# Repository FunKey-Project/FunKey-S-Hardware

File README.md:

## FunKey S Hardware
This repository contains all the hardware design and production files required to build the [FunKey-S retro-gaming console](https://www.funkey-project.com/) electronic PCBA using the [KiCAD ECAD tools](https://kicad.org/).

If you don't want to install these tools but still want to get an idea of what it looks like, you can check the [schematics](https://github.com/FunKey-Project/FunKey-S-Hardware/blob/master/PDF/FunKey%20Schematics.pdf) and the [layout](https://github.com/FunKey-Project/FunKey-S-Hardware/blob/master/PDF/FunKey%20PCB.pdf) in PDF format, the interactive [BOM](https://github.com/FunKey-Project/FunKey-S-Hardware/tree/master/BOM) is directly in HTML format, you can download it and display it in a browser.

The FunKey S is a small foldable retro-gaming console.

Its electronic parts consist in:
 - 1x main PCB (0.8 mm thickness) with components on both sides, the maximum component height above PCB on both sides is 1.5 mm. Current revision for this board is Revision E
 - 1x 1.54” IPS LCD TFT screen with SPI interface and using a custom flex cable
 - 1x 420 mAh 402540 LiPo battery

The FunKey S PCBA Rev. E contains the following main components:
 - 1x Allwinner V3s SoC with integrated 64MB DDR2 DRAM (LQFP128 package)
 - 1x X-Powers AXP209 companion PMIC chip to provide almost all required power supply rails (QFN48 package)
 - 1x Sylergy SY8088 Buck DC/DC SMPS chip to provide the DRAM power supply rail (SOT23-5 package)
 - 1x NXP PCAL6416 I2C GPIO expander to control all buttons and keypads (except Power Key) (QFN24 package)
 - 1x Diodes Inc. PAM8301 mono audio amplifier (TSOT26 package)
 - 1x 24 MHz main crystal
 - 1x 32.768 kHz RTC crystal
 - 1x Standex-Meder MK24 Reed switch for magnet proximity detection
 - 1x LED for charge indication
 - 1x 8 Ω 0.3 W built-in speaker
 - 1x Micro USB edge-mounted connector
 - 1x Micro SD (TF Card) Push/Push low-profile connector
 - 1x Hirose DF37 0.4 mm pitch miniature LCD connector
 - 1x JST 1 mm pitch battery connector
 - 1x 1.27 mm pitch debug UART header (not mounted)

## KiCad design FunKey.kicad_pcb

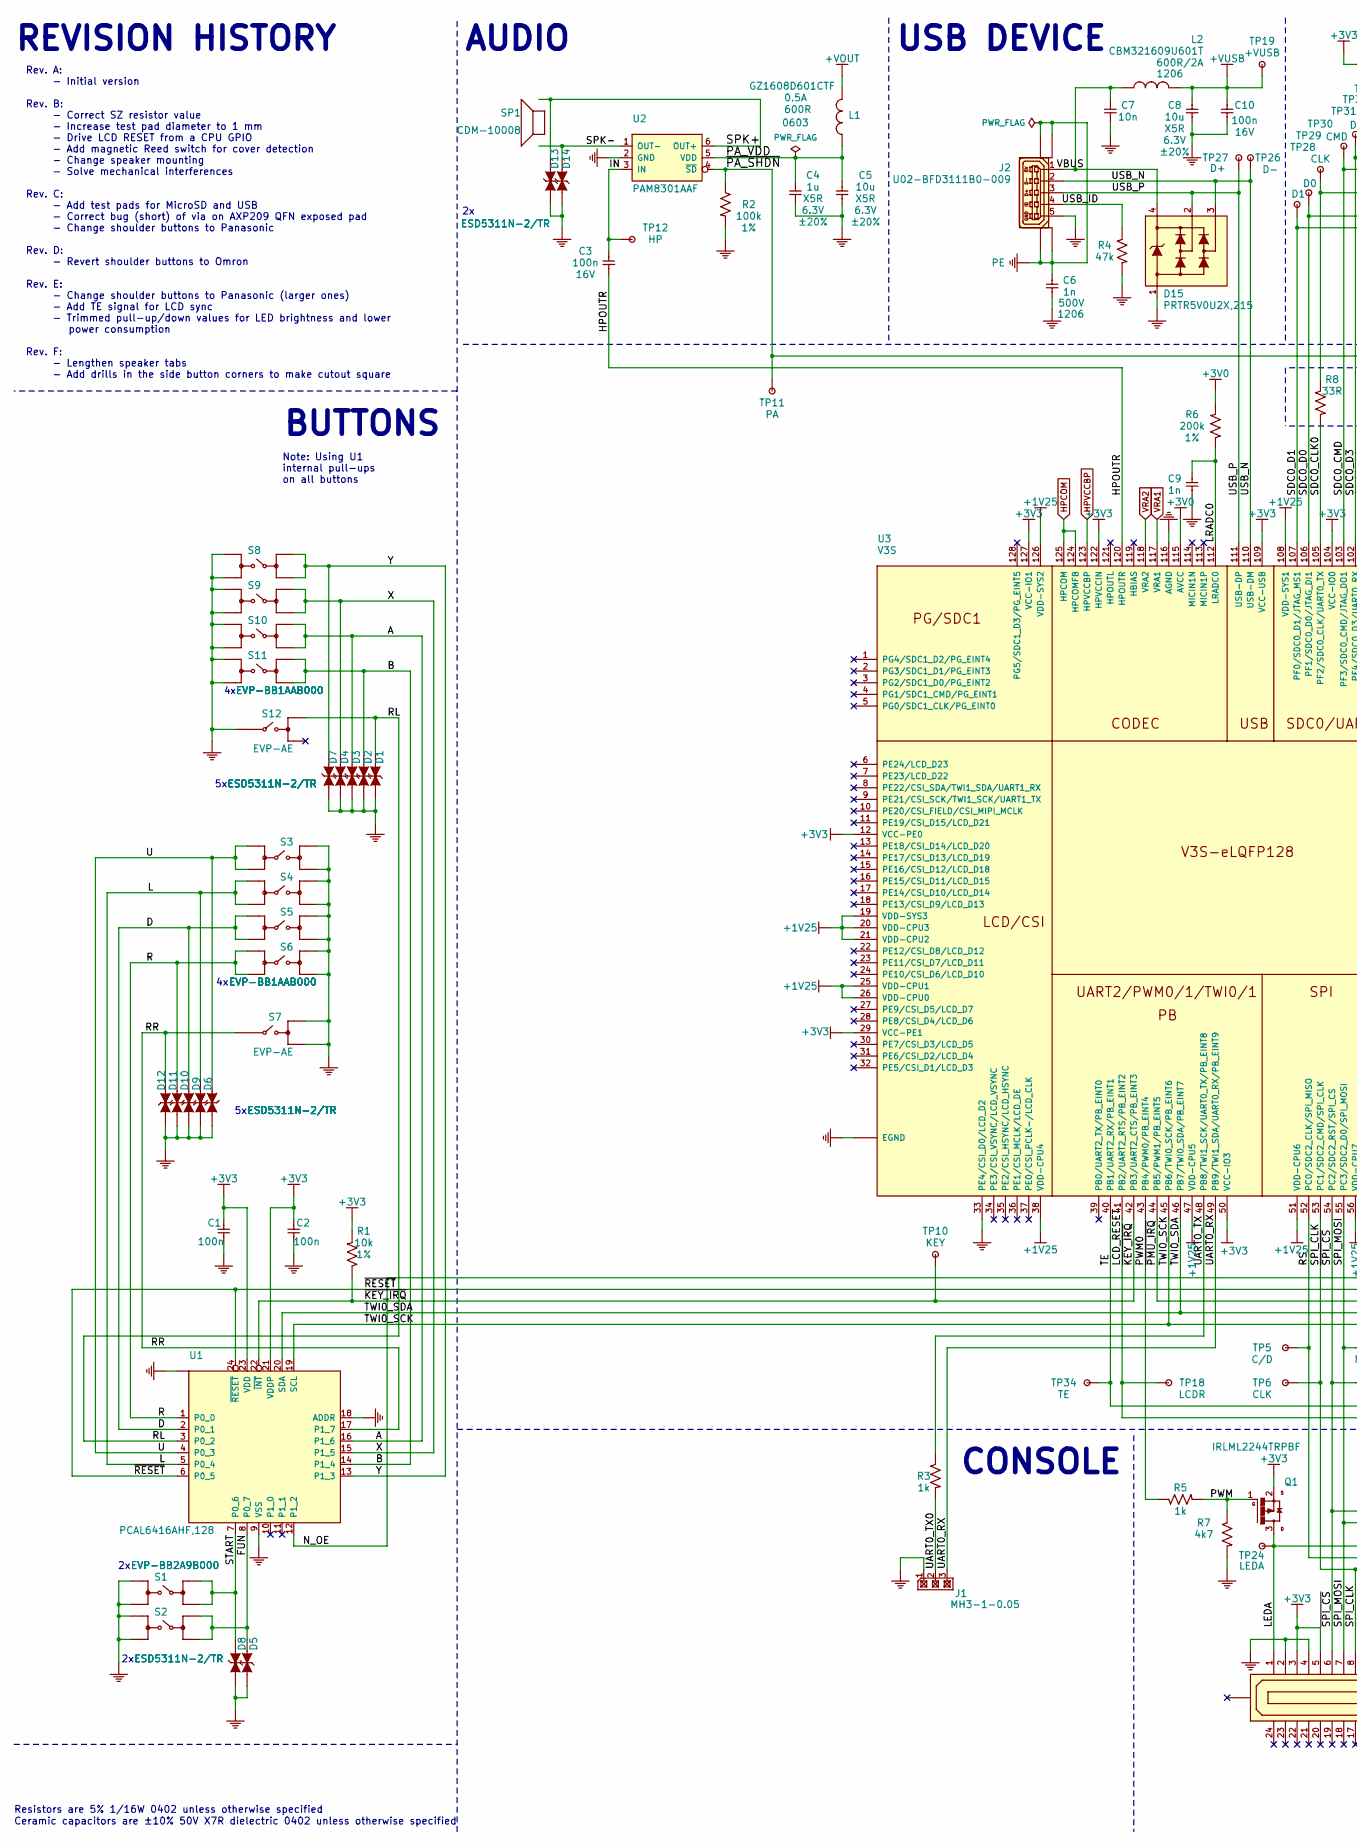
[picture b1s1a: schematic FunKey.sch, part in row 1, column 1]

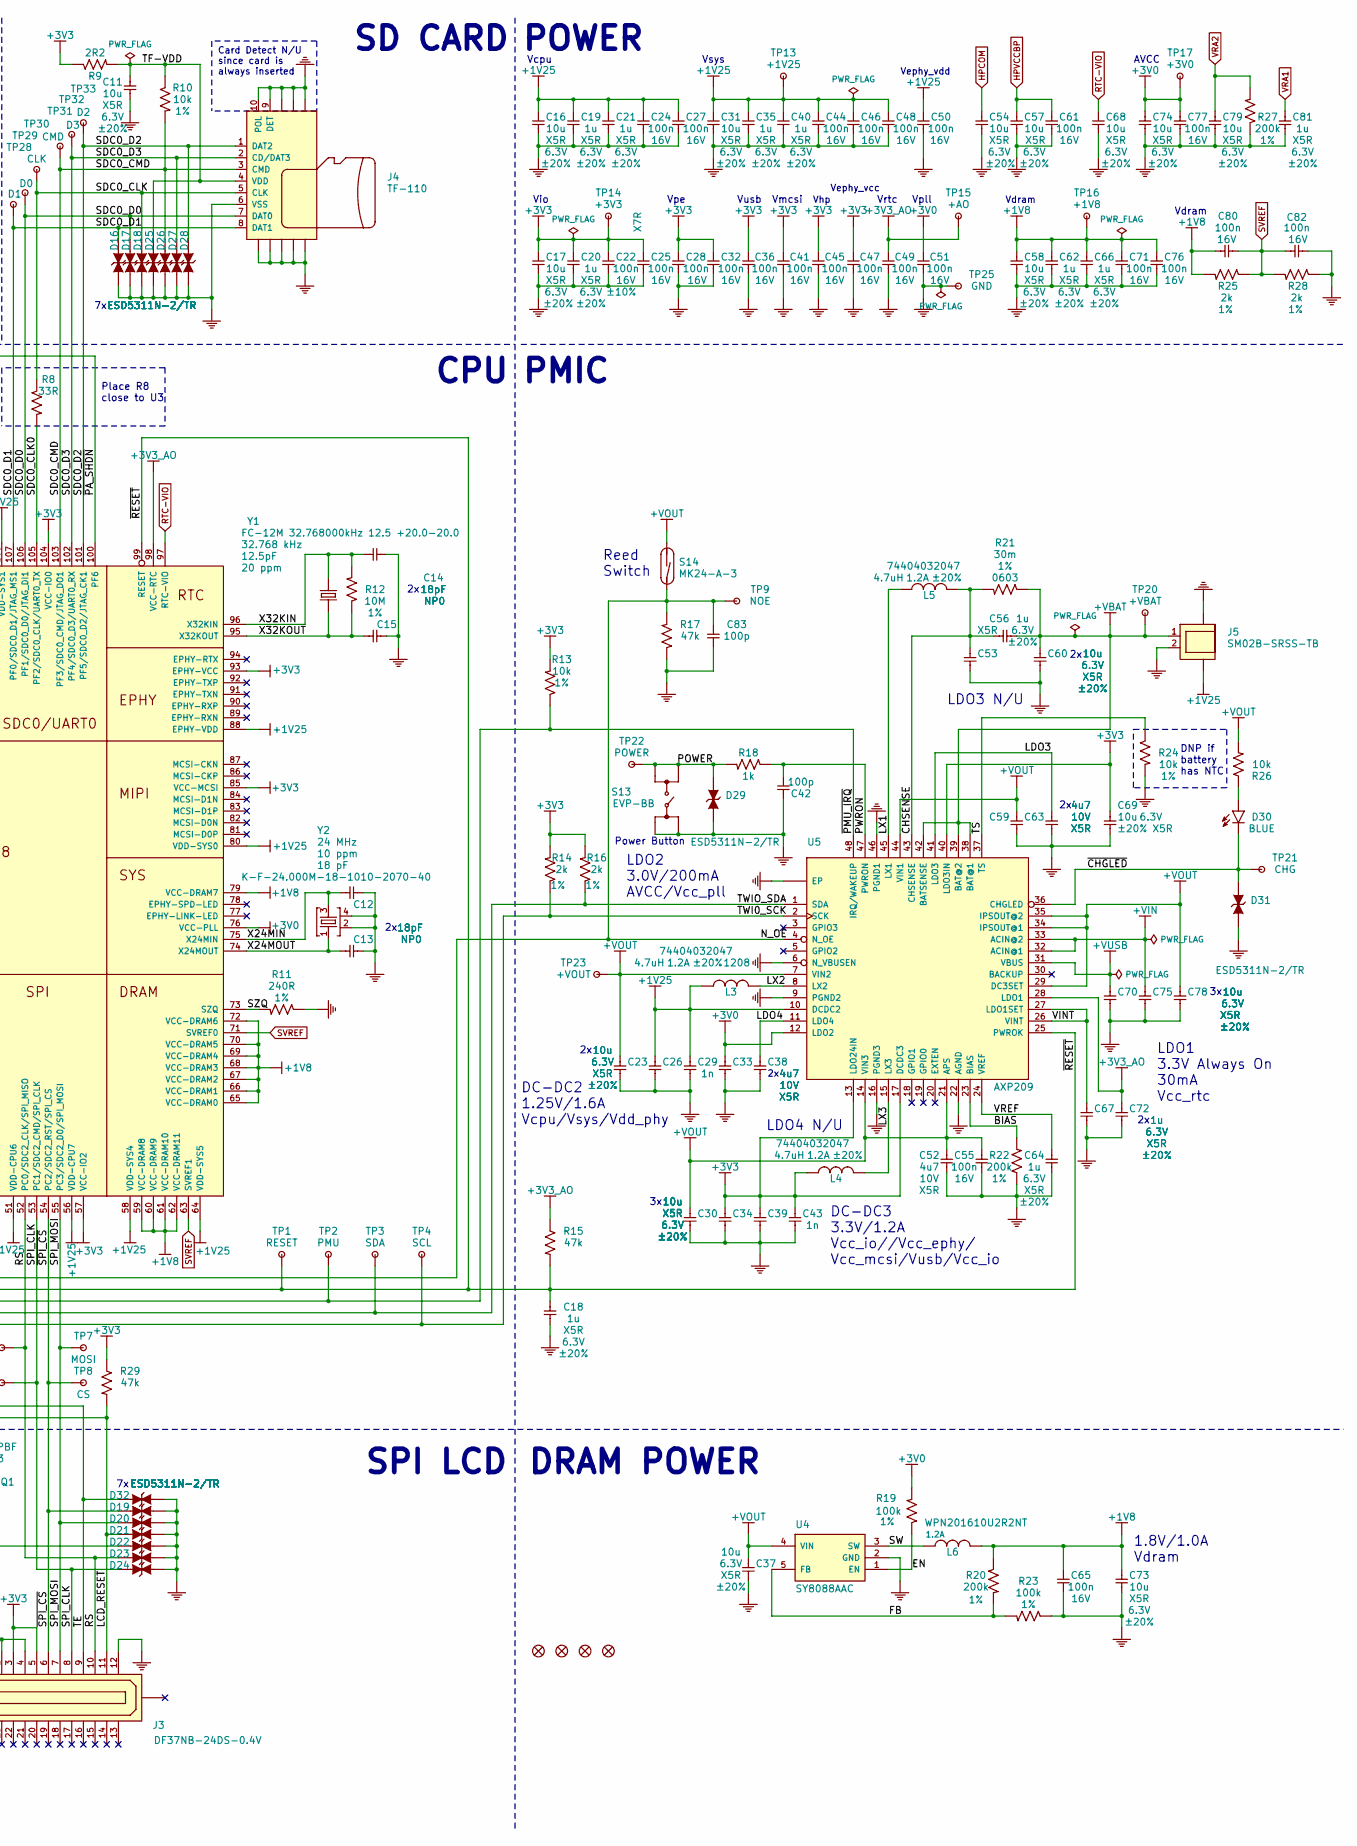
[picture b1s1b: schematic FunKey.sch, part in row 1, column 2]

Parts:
C1, C2, C3, C10, C22, C24, C25, C27, C28, C32, C36, C41, C44, C45, C46, C47, C48, C49, C50, C51, C55, C61, C65, C71, C76, C77, C80, C82: 100n; C0402; PARTNO C0402_100n_X7R_10%_CER_16V
C4, C18, C19, C20, C21, C35, C40, C56, C62, C64, C66, C67, C72, C81: 1u; C0402; PARTNO C0402_1u_X5R_20%_CER_6V3
C5, C8, C11, C16, C17, C23, C26, C30, C31, C34, C37, C39, C53, C54, C57, C58, C60, C68, C69, C70, C73, C74, C75, C78, C79: 10u; C0402; PARTNO C0402_10u_X5R_20%_CER_6V3
C6: 1n; C1206; PARTNO C1206_1n_X7R_10%_CER_500V
C7: 10n; C0402; PARTNO C0402_10n_X7R_10%_CER_50V
C9, C29, C43: 1n; C0402; PARTNO C0402_1n_X7R_10%_CER_50V
C12, C13, C14, C15: 18pF; C0402; PARTNO C0402_18p_NP0_5%_CER_50V
C33, C38, C52, C59, C63: 4u7; C0402; PARTNO C0402_4u7_X5R_10%_CER_10V
C42, C83: 100p; C0402; PARTNO C0402_100p_X7R_10%_CER_50V
D1, D2, D3, D4, D5, D6, D7, D8, D9, D10, D11, D13, D14, D16, D17, D18, D19, D20, D21, D22, D23, D24, D25, D26, D27, D28, D29, D31, D32: ESD5311N-2/TR; ESD0402; PARTNO ESD0402_5V5_BIDIR
D12: ESD5311N-2/TR; ESD0402
D15: PRTR5V0U2X,215; SOT143B; PARTNO PRTR5V0U2X,215
D30: BLUE; LED0402; PARTNO LED0402-BLUE
F1, F2, F3, F4: FIDUCIAL
J1: MH3-1-0.05; PARTNO MH3-1-0.05
J2: U02-BFD3111B0-009; PARTNO U02-BFD3111B0-009
J3: DF37NB-24DS-0.4V; PARTNO DF37NB-24DS-0.4V
J4: TF-110; PARTNO TF-110
J5: SM02B-SRSS-TB; PARTNO SM02B-SRSS-TB
L1: GZ1608D601CTF; FB0603; PARTNO FB0603_600R_25%
L2: CBM321609U601T; FB1206; PARTNO FB1206_600R_25%
L3, L4, L5: 74404032047; WE-LQS; PARTNO 74404032047
L6: WPN201610U2R2NT; L1008; PARTNO L1008
Q1: IRLML2244TRPBF; SOT23-3; PARTNO IRLML2244TRPBF
R1, R10, R13, R24, R26: 10k; R0402; PARTNO R0402_10k_1%_62.5mW
R2, R19, R23: 100k; R0402; PARTNO R0402_100k_1%_62.5mW
R3, R5, R18: 1k; R0402; PARTNO R0402_1k_5%_62.5mW
R4, R15, R17, R29: 47k; R0402; PARTNO R0402_47k_5%_62.5mW
R6, R20, R22, R27: 200k; R0402; PARTNO R0402_200k_1%_62.5mW
R7: 4k7; R0402; PARTNO R0402_4k7_5%_62.5mW
R8: 33R; R0402; PARTNO R0402_33R_5%_62.5mW
R9: 2R2; R0402; PARTNO R0402_2R2_5%_62.5mW
R11: 240R; R0402; PARTNO R0402_240R_1%_62.5mW
R12: 10M; R0402; PARTNO R0402_10M_1%_62.5mW
R14, R16, R25, R28: 2k; R0402; PARTNO R0402_2k_1%_62.5mW
R21: 30m; R0603; PARTNO R0603_30m_1%_333mW
S1, S2: EVP-BB2A9B000; EVP-BB; PARTNO EVP-BB2A9B000
S3, S4, S5, S6, S8, S9, S10, S11: EVP-BB1AAB000; EVP-BB; PARTNO EVP-BB1AAB000
S7, S12: EVP-AE; PARTNO EVP-AE
S13: EVP-BB; PARTNO EVP-BB2A9B000
S14: MK24-A-3; MK24; PARTNO MK24-A-3
SP1: CDM-10008; PARTNO CDM-10008
TP1: RESET; TEST_PAD
TP2: PMU; TEST_PAD
TP3: SDA; TEST_PAD
TP4: SCL; TEST_PAD
TP5: C/D; TEST_PAD
TP6, TP30: CLK; TEST_PAD
TP7: MOSI; TEST_PAD
TP8: CS; TEST_PAD
TP9: NOE; TEST_PAD
TP10: KEY; TEST_PAD
TP11: PA; TEST_PAD
TP12: HP; TEST_PAD
TP13: +1V25; TEST_PAD
TP14: +3V3; TEST_PAD
TP15: +AO; TEST_PAD
TP16: +1V8; TEST_PAD
TP17: +3V0; TEST_PAD
TP18: LCDR; TEST_PAD
TP19: +VUSB; TEST_PAD
TP20: +VBAT; TEST_PAD
TP21: CHG; TEST_PAD
TP22: POWER; TEST_PAD
TP23: +VOUT; TEST_PAD
TP24: LEDA; TEST_PAD
TP25: GND; TEST_PAD
TP26: D-; TEST_PAD
TP27: D+; TEST_PAD
TP28: D1; TEST_PAD
TP29: D0; TEST_PAD
TP31: CMD; TEST_PAD
TP32: D3; TEST_PAD
TP33: D2; TEST_PAD
TP34: TE; TEST_PAD
U1: PCAL6416AHF,128; QFN24; PARTNO PCAL6416AHF,128
U2: PAM8301AAF; TSOT26; PARTNO PAM8301AAF
U3: V3S; ELQFP-128
U4: SY8088AAC; SOT23-5; PARTNO SY8088AAC
U5: AXP209; QFN48; PARTNO AXP209
Y1: FC-12M 32.768000kHz 12.5 +20.0-20.0; FC-12M; PARTNO FC-12M_32K768_12.5PF_20PPM
Y2: K-F-24.000M-18-1010-2070-40; CRYSTAL_32X25; PARTNO XTAL3225_4P_24M_18PF_10PPM

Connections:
+1V8: C58.1, C62.1, C65.2, C66.1, C71.2, C73.2, C76.2, C80.2, L6.2, R20.1, R25.2, TP16.1, U3.59 (VCC-DRAM8), U3.60 (VCC-DRAM9), U3.61 (VCC-DRAM10), U3.62 (VCC-DRAM11), U3.65 (VCC-DRAM0), U3.66 (VCC-DRAM1), U3.67 (VCC-DRAM2), U3.68 (VCC-DRAM3), U3.69 (VCC-DRAM4), U3.70 (VCC-DRAM5), U3.72 (VCC-DRAM6), U3.79 (VCC-DRAM7)
+1V25: C16.1, C19.1, C21.1, C24.2, C26.2, C27.2, C29.2, C31.1, C35.1, C40.1, C44.2, C46.2, C48.2, C50.2, J5.G$2 (G@2), L3.2, TP13.1, U3.19 (VDD-SYS3), U3.20 (VDD-CPU3), U3.21 (VDD-CPU2), U3.25 (VDD-CPU1), U3.26 (VDD-CPU0), U3.38 (VDD-CPU4), U3.47 (VDD-CPU5), U3.51 (VDD-CPU6), U3.56 (VDD-CPU7), U3.58 (VDD-SYS4), U3.64 (VDD-SYS5), U3.80 (VDD-SYS0), U3.88 (EPHY-VDD), U3.108 (VDD-SYS1), U3.126 (VDD-SYS2), U5.10 (DCDC2)
+3V0: C33.2, C51.2, C74.1, C77.2, R6.2, R19.2, TP17.1, U3.76 (VCC-PLL), U3.115 (AVCC), U5.12 (LDO2)
+3V3: C1.2, C2.2, C17.1, C20.1, C22.2, C25.2, C28.2, C32.2, C34.1, C36.2, C39.2, C41.2, C43.2, C45.2, C47.2, C69.1, J3.3, J3.5, L4.1, Q1.2 (S), R1.2, R9.1, R13.2, R14.2, R16.2, R29.1, TP14.1, U1.21 (VDDP), U1.23 (VDD), U3.12 (VCC-PE0), U3.29 (VCC-PE1), U3.50 (VCC-IO3), U3.57 (VCC-IO2), U3.85 (VCC-MCSI), U3.93 (EPHY-VCC), U3.104 (VCC-IO0), U3.109 (VCC-USB), U3.122 (HPVCCIN), U3.127 (VCC-IO1), U5.13 (LDO24IN), U5.17 (DCDC3), U5.40 (LDO3IN)
+3V3_AO: C49.2, C72.1, R15.1, TP15.1, U3.98 (VCC-RTC), U5.28 (LDO1)
+VBAT: C56.2, C60.1, J5.1, R21.1, TP20.1, U5.38 (BAT@1), U5.39 (BAT@2), U5.42 (BATSENSE)
+VIN: C75.1, U5.32 (ACIN@1), U5.33 (ACIN@2)
+VOUT: C23.2, C30.2, C37.2, C52.1, C55.2, C59.1, C78.1, L1.1, R26.2, S14.1 (A), TP23.1, U4.4 (VIN), U5.7 (VIN2), U5.14 (VIN3), U5.21 (APS), U5.29 (DC3SET), U5.34 (IPSOUT@1), U5.35 (IPSOUT@2), U5.44 (VIN1)
+VUSB: C8.2, C10.2, C70.1, L2.2, TP19.1, U5.31 (VBUS)
/A: D3.1, S10.B, S10.B', U1.16 (P1_6)
/B: D2.1, S11.B, S11.B', U1.14 (P1_4)
/BIAS: R22.2, U5.23 (BIAS)
/CHSENSE: C53.1, C56.1, L5.2, R21.2, U5.43 (CHSENSE)
/D: D10.1, S5.B, S5.B', U1.2 (P0_1)
/EN: R19.1, U4.1 (EN)
/FB: R20.2, R23.2, U4.5 (FB)
/FUN: D5.1, S2.B, S2.B', U1.8 (P0_7)
/HPOUTR: C3.1, U3.120 (HPOUTR)
/IN: C3.2, TP12.1, U2.3 (IN)
/L: D9.1, S4.B, S4.B', U1.5 (P0_4)
/LCD_RESET: D21.1, J3.11, R29.2, TP18.1, U3.41 (PB2/UART2_RTS/PB_EINT2)
/LDO3: C63.1, U5.41 (LDO3)
/LDO4: C38.2, U5.11 (LDO4)
/LEDA: D22.1, J3.1, Q1.3 (D), TP24.1
/LRADC0: C9.2, R6.1, U3.112 (LRADC0)
/LX1: L5.1, U5.45 (LX1)
/LX2: L3.1, U5.8 (LX2)
/LX3: L4.2, U5.15 (LX3)
/N_OE: C83.1, R17.2, S14.2 (B), TP9.1, U1.12 (P1_2), U5.4 (N_OE)
/PA_VDD: C4.1, C5.2, L1.2, U2.5 (VDD)
/POWER: D29.1, R18.2, S13.A, S13.A', TP22.1
/PWM: Q1.1 (G), R5.2, R7.1
/PWM0: R5.1, U3.43 (PB4/PWM0/PB_EINT4)
/PWRON: C42.1, R18.1, U5.47 (PWRON)
/R: D11.1, S6.B, S6.B', U1.1 (P0_0)
/RL: D1.1, S12.1 (A), U1.3 (P0_2)
/RR: D12.1, S7.2 (B'), U1.17 (P1_7)
/RS: D23.1, J3.10, TP5.1, U3.52 (PC0/SDC2_CLK/SPI_MISO)
/SDC0_CLK: D18.1, J4.5 (CLK), R8.1, TP30.1
/SDC0_CLK0: R8.2, U3.105 (PF2/SDC0_CLK/UART0_TX)
/SDC0_CMD: D26.1, J4.3 (CMD), R10.2, TP31.1, U3.103 (PF3/SDC0_CMD/JTAG_DO1)
/SDC0_D0: D17.1, J4.7 (DAT0), TP29.1, U3.106 (PF1/SDC0_D0/JTAG_DI1)
/SDC0_D1: D16.1, J4.8 (DAT1), TP28.1, U3.107 (PF0/SDC0_D1/JTAG_MS1)
/SDC0_D2: D28.1, J4.1 (DAT2), TP33.1, U3.101 (PF5/SDC0_D2/JTAG_CK1)
/SDC0_D3: D27.1, J4.2 (CD/DAT3), TP32.1, U3.102 (PF4/SDC0_D3/UART0_RX)
/SPI_CLK: D24.1, J3.8, TP6.1, U3.53 (PC1/SDC2_CMD/SPI_CLK)
/SPI_MOSI: D20.1, J3.7, TP7.1, U3.55 (PC3/SDC2_D0/SPI_MOSI)
/SPK+: D13.1, U2.6 (OUT+)
/SPK-: D14.1, U2.1 (OUT-)
/START: D8.1, S1.B, S1.B', U1.7 (P0_6)
/SW: L6.1, U4.3 (SW)
/SZQ: R11.2, U3.73 (SZQ)
/TE: D32.1, J3.9, TP34.1, U3.40 (PB1/UART2_RX/PB_EINT1)
/TF-VDD: C11.2, D25.1, J4.4 (VDD), R9.2, R10.1
/TS: R24.1, U5.37 (TS)
/TWI0_SCK: R14.1, TP4.1, U1.19 (SCL), U3.45 (PB6/TWI0_SCK/PB_EINT6), U5.2 (SCK)
/TWI0_SDA: R16.1, TP3.1, U1.20 (SDA), U3.46 (PB7/TWI0_SDA/PB_EINT7), U5.1 (SDA)
/U: D6.1, S3.B, S3.B', U1.4 (P0_3)
/UART0_RX: J1.3, U3.49 (PB9/TWI1_SDA/UART0_RX/PB_EINT9)
/UART0_TX: R3.1, U3.48 (PB8/TWI1_SCK/UART0_TX/PB_EINT8)
/UART0_TX0: J1.2, R3.2
/USB_ID: J2.4, R4.1
/USB_N: D15.3, J2.2, TP26.1, U3.110 (USB-DM)
/USB_P: D15.2, J2.3, TP27.1, U3.111 (USB-DP)
/VBUS: C7.1, D15.4, J2.1, L2.1
/VINT: C67.1, U5.26 (VINT), U5.27 (LDO1SET)
/VREF: C64.2, U5.24 (VREF)
/X: D4.1, S9.B, S9.B', U1.15 (P1_5)
/X24MIN: C12.2, U3.75 (X24MIN), Y2.3
/X24MOUT: C13.2, U3.74 (X24MOUT), Y2.1
/X32KIN: C14.2, R12.2, U3.96 (X32KIN), Y1.2
/X32KOUT: C15.2, R12.1, U3.95 (X32KOUT), Y1.1
/Y: D7.1, S8.B, S8.B', U1.13 (P1_3)
/~CHGLED: D30.1 (C), D31.1, TP21.1, U5.36 (CHGLED)
/~KEY_IRQ: R1.1, TP10.1, U1.22 (~INT), U3.42 (PB3/UART2_CTS/PB_EINT3)
/~PA_SHDN: R2.1, TP11.1, U2.4 (~SD), U3.100 (PF6)
/~PMU_IRQ: R13.1, TP2.1, U3.44 (PB5/PWM1/PB_EINT5), U5.48 (IRQ/WAKEUP)
/~RESET: C18.1, R15.2, TP1.1, U1.6 (P0_5), U1.24 (~RESET), U3.99 (RESET), U5.25 (PWROK)
/~SPI_CS: D19.1, J3.6, TP8.1, U3.54 (PC2/SDC2_RST/SPI_CS)
GND: C1.1, C2.1, C4.2, C5.1, C6.2, C7.2, C8.1, C9.1, C10.1, C11.1, C12.1, C13.1, C14.1, C15.1, C16.2, C17.2, C18.2, C19.2, C20.2, C21.2, C22.1, C23.1, C24.1, C25.1, C26.1, C27.1, C28.1, C29.1, C30.1, C31.2, C32.1, C33.1, C34.2, C35.2, C36.1, C37.1, C38.1, C39.1, C40.2, C41.1, C42.2, C43.1, C44.1, C45.1, C46.1, C47.1, C48.1, C49.1, C50.1, C51.1, C52.2, C53.2, C54.2, C55.1, C57.2, C58.2, C59.2, C60.2, C61.1, C62.2, C63.2, C64.1, C65.1, C66.2, C67.2, C68.2, C69.2, C70.2, C71.1, C72.2, C73.1, C74.2, C75.2, C76.1, C77.1, C78.2, C79.2, C81.2, C82.1, C83.2, D1.2, D2.2, D3.2, D4.2, D5.2, D6.2, D7.2, D8.2, D9.2, D10.2, D11.2, D12.2, D13.2, D14.2, D15.1, D16.2, D17.2, D18.2, D19.2, D20.2, D21.2, D22.2, D23.2, D24.2, D25.2, D26.2, D27.2, D28.2, D29.2, D31.2, D32.2, J1.1, J2.5, J3.2, J3.4, J3.12, J4.6 (VSS), J4.9 (DET), J4.10 (POL), J4.G$1 (GND@1), J4.G$2 (GND@2), J4.G$3 (GND@3), J4.G$4 (GND@4), J4.G$5 (GND@5), J4.G$6 (GND@6), J4.G$7 (GND@7), J4.G$8 (GND@8), J5.2, J5.G$1 (G@1), R2.2, R4.2, R7.2, R11.1, R17.1, R22.1, R23.1, R24.2, R27.1, R28.1, S1.A, S1.A', S2.A, S2.A', S3.A, S3.A', S4.A, S4.A', S5.A, S5.A', S6.A, S6.A', S7.1 (A), S7.1' (A'), S8.A, S8.A', S9.A, S9.A', S10.A, S10.A', S11.A, S11.A', S12.2 (B'), S13.B, S13.B', TP25.1, U1.9 (VSS), U1.18 (ADDR), U1.25 (PAD), U2.2 (GND), U3.33 (PE4/CSI_D0/LCD_D2), U3.116 (AGND), U3.GND$1 (EGND), U3.GND$2 (EGND), U3.GND$3 (EGND), U3.GND$4 (EGND), U3.GND$5 (EGND), U3.GND$6 (EGND), U3.GND$7 (EGND), U3.GND$8 (EGND), U3.GND$9 (EGND), U4.2 (GND), U5.6 (N_VBUSEN), U5.9 (PGND2), U5.16 (PGND3), U5.22 (AGND), U5.46 (PGND1), U5.GND$1 (EP), U5.GND$2 (EP), U5.GND$3 (EP), U5.GND$4 (EP), U5.GND$5 (EP), U5.GND$6 (EP), U5.GND$7 (EP), U5.GND$8 (EP), U5.GND$9 (EP), Y2.2, Y2.4
HPCOM: C54.1, U3.124 (HPCOMFB), U3.125 (HPCOM)
HPVCCBP: C57.1, C61.2, U3.123 (HPVCCBP)
unnamed: D30.2 (A), R26.1
PE: C6.1, J2.S$1 (M0), J2.S$2 (M1), J2.S$3 (M2), J2.S$4 (M3)
RTC-VIO: C68.1, U3.97 (RTC-VIO)
SVREF: C80.1, C82.2, R25.1, R28.2, U3.63 (SVREF1), U3.71 (SVREF0)
VRA1: C81.1, U3.117 (VRA1)
VRA2: C79.1, R27.2, U3.118 (VRA2)

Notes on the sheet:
Ceramic capacitors are ±10% 50V X7R dielectric 0402 unless otherwise specified
Resistors are 5% 1/16W 0402 unless otherwise specified
POWER
DNP if battery has NTC
Vusb
Vmcsi
Vrtc
Vpll
Vhp
Vcpu
Vsys
Vio
Vdram
AVCC
SD CARD
AUDIO
DC-DC2 1.25V/1.6A Vcpu/Vsys/Vdd_phy
DC-DC3 3.3V/1.2A Vcc_io//Vcc_ephy/ Vcc_mcsi/Vusb/Vcc_io
LDO4 N/U
LDO3 N/U
LDO1 3.3V Always On 30mA Vcc_rtc
LDO2 3.0V/200mA AVCC/Vcc_pll
1.8V/1.0A Vdram
Place R8 close to U3
Card Detect N/U since card is always inserted
CONSOLE
CPU
DRAM POWER
PMIC
SPI LCD
Power Button
Vpe
Vephy_vcc
Vephy_vdd
BUTTONS
Note: Using U1 internal pull-ups on all buttons
Reed Switch
USB DEVICE
REVISION HISTORY
Rev. A: - Initial version Rev. B: - Correct SZ resistor value - Increase test pad diameter to 1 mm - Drive LCD RESET from a CPU GPIO - Add magnetic Reed switch for cover detection - Change speaker mounting - Solve mechanical interferences Rev. C: - Add test pads for MicroSD and USB - Correct bug (s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

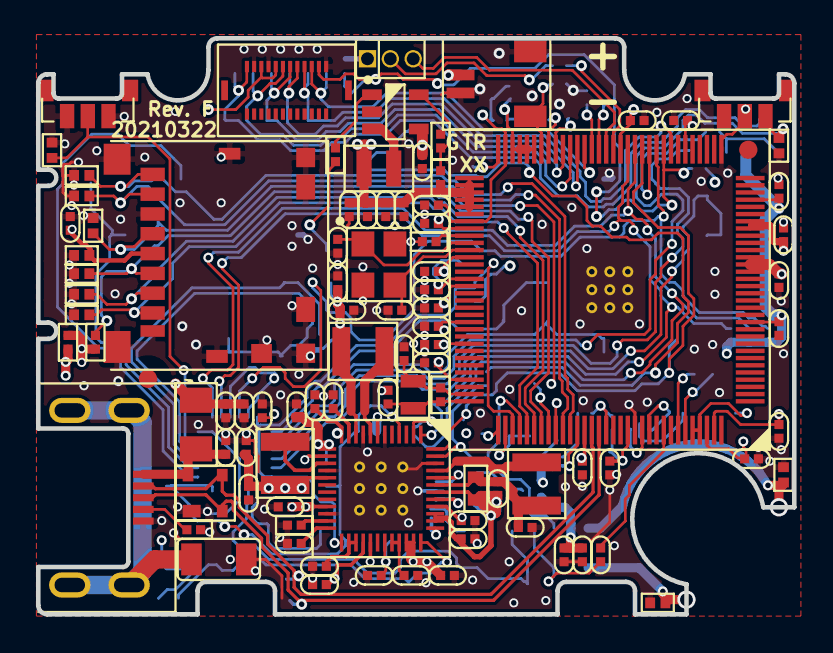
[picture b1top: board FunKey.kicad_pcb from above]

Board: 4 copper layers, 42.0 x 32.0 mm, 217 parts (0 on the bottom side), 88 nets.

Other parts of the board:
DRILEGEND: DRILEGEND

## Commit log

2020-11-29 update PCB pictures
2020-11-30 use Protel extensions for gerber files
2020-12-01 add LCD display datasheet
2020-12-04 FunKey S Rev. E public release
2021-07-27 Revision F with 0.3mm increased length speaker tabs and added drills in the side button corners to make cutout square
2022-02-09 Update LICENCE

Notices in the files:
FunKey.kicad_pcb:
© 2017-2021, All rights reserved.
FunKey.sch:
© 2017-2021 Michel Stempin, All rights reserved.
README.md:
licensebuttons by-nc-sa
